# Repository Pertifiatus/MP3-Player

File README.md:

# MP3-Player

A compact **DIY music player**, smaller than an iPod Touch, built around a Raspberry Pi Compute Module 4 on a custom PCB. It syncs your **YouTube Music** library straight to the device, no home server needed.

## Concept

- **Front:** round GC9A01 display for menus and navigation
- **Back:** monochrome SSD1306 OLED for music visualizations
- **Audio:** mainly Bluetooth A2DP, plus a 3.5 mm headphone jack (ES8388 codec)
- **Controls:** button box (SX1509 GPIO expander) + IMU (QMI8658A) for orientation and shake gestures
- **Power:** Li-ion battery, USB-C charging (RT9466) with an 80% charge limit, fuel gauge (MAX17048), soft power button
- **Lighting:** SK6812 status ring

## Hardware

| Part | Details |
|---|---|
| Compute | Raspberry Pi CM4 Lite Wireless (boots from microSD), on 2× Hirose mezzanine connectors |
| Power | TPS63020 buck-boost, RT9466 charger, MAX17048 fuel gauge |
| Audio | ES8388 codec over I2S |
| Displays | GC9A01 (SPI0), SSD1306 (SPI4) |
| PCBs | Main board + ButtonBox, designed in KiCad (`KiCad/Projekt 1`) |
| Case | Fusion 360 (`CAD/Player.f3z`) |

## Software (`Software/`)

Python on Raspberry Pi OS, running as systemd services:

| File | Purpose |
|---|---|
| `main.py` | Main UI loop (front display, buttons, IMU) |
| `player.py` | Playback |
| `sync_youtube.py` | YouTube Music library sync |
| `connectivity.py` | WiFi / Bluetooth connections |
| `ui_state.py`, `ui_render.py` | UI state machine and rendering |
| `ui_views.py`, `ui_common.py` | Screen content as plain data, shared drawing helpers |
| `themes/` | 8 switchable designs (Einstellungen → Anzeige → Design): Klassik, Cybercore, Y2K, Glas, Neumorph, Bento, Pixelhaus, Cyberpunk |
| `preview_themes.py` | Preview sheet per design (`previews/`), `--bench` render timings |
| `fonts/`, `assets/` | Bundled OFL fonts, Pixelhaus house image |
| `buttonbox.py`, `qmi8658.py`, `es8388.py`, `max17048.py`, `rt9466.py` | Hardware drivers |
| `charge_control.py`, `power_button.py` | Charging logic and soft shutdown |
| `led_control.py`, `led_service.py` | Status ring LEDs |
| `setup_pi.sh`, `*.service`, `sdcard-boot-*` | Pi setup and boot configuration |
| `test_*.py` | Tests |

## Status

Work in progress. Board 2 boots reliably; the software bring-up and debugging of battery operation are ongoing. Detailed notes on hardware, pinout, `config.txt` and lessons learned are in [`CLAUDE.md`](CLAUDE.md) and [`Software/NOTES_FOR_PER.md`](Software/NOTES_FOR_PER.md).

## Repository structure

```
CAD/        Fusion 360 case
KiCad/      Main board + ButtonBox (schematics, PCB, 3D models)
Software/   Python application, drivers, services, tests
docs/       Design specs and plans (status ring, quick connect, design themes)
```

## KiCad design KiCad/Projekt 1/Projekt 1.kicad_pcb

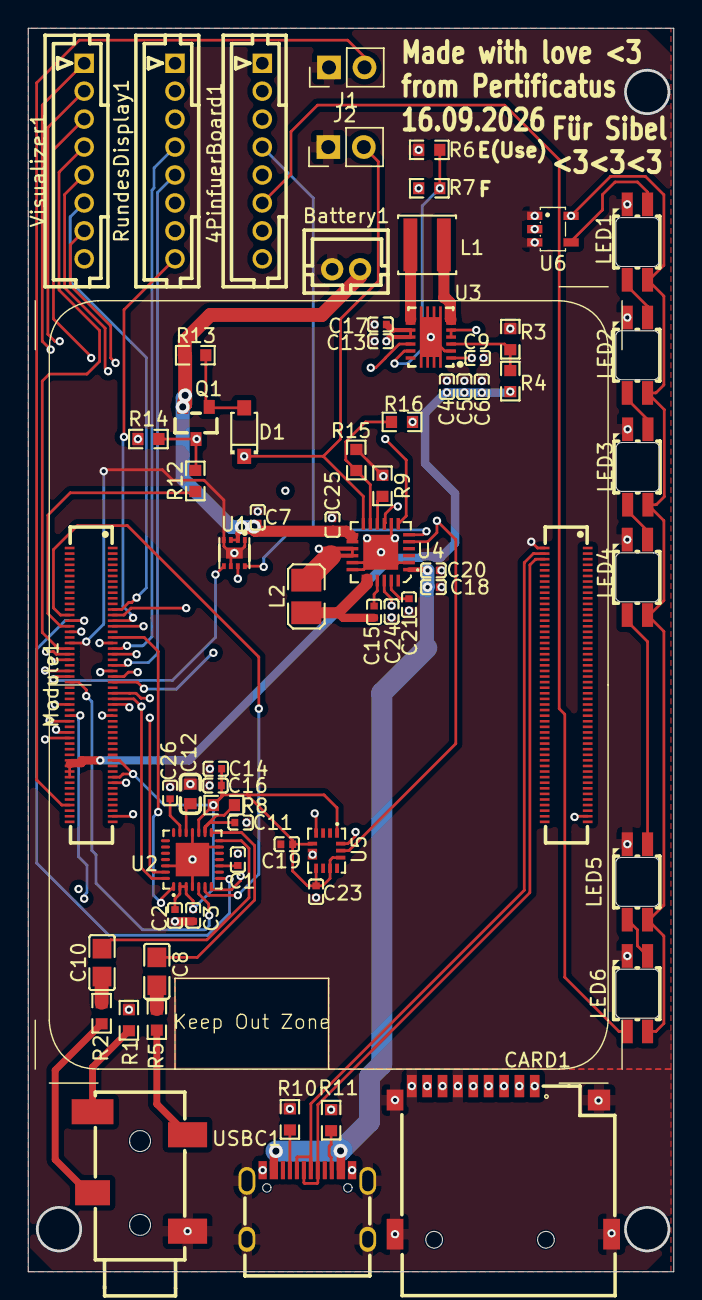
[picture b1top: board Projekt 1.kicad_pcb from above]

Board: 4 copper layers, 46.2 x 89.0 mm, 67 parts (0 on the bottom side), 74 nets.

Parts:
4PinfuerBoard1: CONN-TH_B8B-PH-K-S-LF-SN
AUDIO1: AUDIO-SMD_PJ-327C-4A
Battery1: CONN-TH_B2B-PH-K-S
C1, C18, C20: 2.2uF; C0402
C2, C3, C7, C9, C11, C14, C16, C19, C23: 100nF; C0402
C4, C5, C6: 22uF; C0402
C8, C10: 100uF; C0805
C12: 1uF; C0603
C13, C17, C25: 10uF; C0402
C15: 47nF; C0402
C21, C24, C26: 4.7uF; C0402
CARD1: TF-SMD_TF-PUSH
D1: SOD-123F_L2.7-W1.6-LS3.8-RD
J1: Boot Button; PinHeader_1x02_P2.54mm_Vertical
J2: Switch; PinHeader_1x02_P2.54mm_Vertical
L1: 1.5uH; IND-SMD_L4.0-W4.0-A
L2: 1uH; L2520
LED1, LED2, LED3, LED4, LED5, LED6: LED-SMD_4P-L3.2-W2.8-LS5.9_SK6812MINI-E
Module1: ComputeModule4-CM4; CONN-SMD_DF40HC-3.0-100DS-0.4V-51
Q1: SOT-23_L2.9-W1.3-P1.90-LS2.4-BR
R1, R10, R11: 5.1kΩ; R0603
R2, R5: 33Ω; R0603
R3: 180kΩ; R0603
R4: 1.6MΩ; R0603
R6, R7: 0Ω; R0603
R8: 10Ω; R0603
R9: 178Ω; R0603
R12: 220Ω; R0603
R13, R14: 100kΩ; R0603
R15, R16: 50kΩ; R0603
RundesDisplay1: CONN-TH_B8B-PH-K-S-LF-SN
U1: TDFN-8_L2.0-W2.0-P0.50-BL-EP1.2
U2: QFN-28_L4.0-W4.0-P0.45-BL-EP
U3: VSON-14_L4.0-W3.0-P0.50-BL-EP_TI_DSJ
U4: WQFN-24_L4.0-W4.0-P0.50-TL-EP2.5
U5: LGA-14_L3.0-W2.5-P0.50-TL
U6: SOT-23-5_L3.0-W1.7-P0.95-LS2.8-BR
USBC1: USB-C_SMD-TYPE-C-31-M-12_1
Visualizer1: CONN-TH_B8B-PH-K-S-LF-SN

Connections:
GND: AUDIO1.1, Battery1.2, C1.2, C2.1, C3.1, C4.2, C5.2, C6.2, C7.1, C9.1, C11.2, C12.2, C13.1, C14.2, C16.1, C17.1, C18.1, C19.1, C20.1, C21.2, C23.1, C24.1, C25.1, C26.1, CARD1.6 (VSS), CARD1.10, CARD1.11, CARD1.12, CARD1.13, CARD1.CD, J1.1, J2.1, LED1.1 (GND), LED2.1 (GND), LED3.1 (GND), LED4.1 (GND), LED5.1 (GND), LED6.1 (GND), Module1.35 (ID_SC), Module1.101 (USB_OTG_ID), Module1.198 (GND), R1.2, R3.2, R6.1, R9.1, R10.1, R11.1, R14.1, R15.2, U1.1 (CTG), U1.4 (GND), U1.6 (QSTRT), U1.9 (EP), U2.4 (DGND), U2.13 (HPGND), U2.18 (AGND), U2.26 (CE), U2.29 (EP), U3.2 (GND), U3.15 (PGND), U4.2 (PSEL), U4.8 (OTG), U4.17 (PGND), U4.18 (PGND), U4.25 (EP), U5.6 (GND), U5.7 (GND), U6.1 (OE#), U6.3 (GND), USBC1.1 (EH), USBC1.2 (EH), USBC1.3 (EH), USBC1.4 (EH), USBC1.A1B12 (GND), USBC1.B1A12 (GND)
unnamed: 4PinfuerBoard1.3, Module1.98 (GND), RundesDisplay1.3, Visualizer1.3
unnamed: AUDIO1.2, R5.1
unnamed: AUDIO1.3, R2.1
unnamed: AUDIO1.4, R1.1
unnamed: C8.1, R5.2
unnamed: C10.1, R2.2
unnamed: C15.2, L2.1, U4.19 (LX), U4.20 (LX)
unnamed: CARD1.2 (CD/DAT3), Module1.61 (SD_DAT3)
unnamed: CARD1.5 (CLX), Module1.57 (SD_CLK)
unnamed: CARD1.3 (CMD), Module1.62 (SD_CMD)
unnamed: CARD1.7 (DAT0), Module1.63 (SD_DAT0)
unnamed: CARD1.8 (DAT1), Module1.67 (SD_DAT1)
unnamed: CARD1.1 (DAT2), Module1.69 (SD_DAT2)
unnamed: 4PinfuerBoard1.1, CARD1.4 (VDD), Module1.86 (+3.3v_(Output)), RundesDisplay1.1, Visualizer1.1
unnamed: D1.2 (A), Q1.1 (G), R13.1
unnamed: D1.1 (K), J2.2, Module1.40 (GPIO9), U4.12 (#QON)
unnamed: J1.2, Module1.93 (nRPIBOOT)
unnamed: L1.1, U3.6 (L2), U3.7 (L2)
unnamed: L1.2, U3.8 (L1), U3.9 (L1)
unnamed: LED1.2 (DIN), U6.4 (Y)
unnamed: LED1.4 (DOUT), LED2.2 (DIN)
unnamed: 4PinfuerBoard1.5, C4.1, C5.1, C6.1, LED1.3 (VDD), LED2.3 (VDD), LED3.3 (VDD), LED4.3 (VDD), LED5.3 (VDD), LED6.3 (VDD), Module1.77 (+5v_(Input)), Module1.79 (+5v_(Input)), Module1.81 (+5v_(Input)), Module1.83 (+5v_(Input)), R4.2, U3.4 (VOUT), U3.5 (VOUT), U6.5 (VCC)
unnamed: LED2.4 (DOUT), LED3.2 (DIN)
unnamed: LED3.4 (DOUT), LED4.2 (DIN)
unnamed: LED4.4 (DOUT), LED5.2 (DIN)
unnamed: LED5.4 (DOUT), LED6.2 (DIN)
unnamed: 4PinfuerBoard1.6, LED6.4 (DOUT)
unnamed: 4PinfuerBoard1.4, Module1.58 (GPIO2), U1.8 (SDA), U2.27 (CDATA), U4.6 (SDA), U5.14 (SDA)
unnamed: 4PinfuerBoard1.2, Module1.56 (GPIO3), U1.7 (SCL), U2.28 (CCLK), U4.5 (SCL), U5.13 (SCL)
unnamed: Module1.54 (GPIO4), Visualizer1.7
unnamed: Module1.34 (GPIO5), U2.1 (MCLK)
unnamed: Module1.30 (GPIO6), Visualizer1.5
unnamed: Module1.37 (GPIO7), Visualizer1.4
unnamed: Module1.39 (GPIO8), RundesDisplay1.7
unnamed: Module1.44 (GPIO10), RundesDisplay1.5
unnamed: Module1.38 (GPIO11), RundesDisplay1.4
unnamed: Module1.31 (GPIO12), U6.2 (A)
unnamed: Module1.28 (GPIO13), RundesDisplay1.8
unnamed: Module1.29 (GPIO16), R12.1
unnamed: Module1.50 (GPIO17), U4.9 (CEB)
unnamed: Module1.49 (GPIO18), U2.5 (SCLK)
unnamed: Module1.26 (GPIO19), U2.7 (LRCK)
unnamed: Module1.27 (GPIO20), U2.8 (ASDOUT)
unnamed: Module1.25 (GPIO21), U2.6 (DSDIN)
unnamed: Module1.46 (GPIO22), U4.7 (INT)
unnamed: Module1.47 (GPIO23), U1.5 (ALRT#)
unnamed: Module1.45 (GPIO24), RundesDisplay1.6
unnamed: Module1.41 (GPIO25), RundesDisplay1.2
unnamed: Module1.24 (GPIO26), Visualizer1.6
unnamed: Module1.48 (GPIO27), Visualizer1.2
unnamed: C2.2, C3.2, C14.1, C16.2, C19.2, C23.2, Module1.78 (GPIO_VREF(1.8v/3.3v_Input)), Module1.84 (+3.3v_(Output)), R8.2, U2.2 (DVDD), U2.3 (PVDD), U2.17 (AVDD), U5.1 (SDO/SA0), U5.5 (VDDIO), U5.8 (VDD), U5.10 (CS-AUX), U5.12 (CS)
unnamed: Module1.36 (ID_SD), U5.4 (INT1)
unnamed: Module1.103 (USB2_N), USBC1.A7 (DN1), USBC1.B7 (DN2)
unnamed: Module1.105 (USB2_P), USBC1.A6 (DP1), USBC1.B6 (DP2)
unnamed: Q1.3 (D), R12.2, R14.2, U3.12 (EN)
unnamed: Battery1.1, C7.2, C25.2, Q1.2 (S), R13.2, U1.2 (CELL), U1.3 (VDD), U4.13 (BAT), U4.14 (BAT)
unnamed: C12.1, U2.19 (ADCVREF)
unnamed: C11.1, R8.1, U2.16 (HPVDD)
unnamed: C8.2, U2.15 (LOUT2)
unnamed: C10.2, U2.14 (ROUT2)
unnamed: C26.2, U2.20 (VMID)
unnamed: C1.1, U2.10 (VREF)
unnamed: R3.1, R4.1, U3.3 (FB)
unnamed: R6.2, R7.2, U3.13 (PS/SYNC)
unnamed: C9.2, C13.2, C17.2, L2.2, R7.1, U3.1 (VINA), U3.10 (VIN), U3.11 (VIN), U4.15 (SYS), U4.16 (SYS)
unnamed: C15.1, U4.21 (BTST)
unnamed: R9.2, U4.10 (ILIM)
unnamed: C24.2, R16.1, U4.22 (REGN)
unnamed: R15.1, R16.2, U4.11 (TS)
unnamed: C18.2, C20.2, U4.1 (VBUS), USBC1.A4B9 (VBUS), USBC1.B4A9 (VBUS)
unnamed: C21.1, U4.23 (VMID)
unnamed: R10.2, USBC1.A5 (CC1)
unnamed: R11.2, USBC1.B5 (CC2)

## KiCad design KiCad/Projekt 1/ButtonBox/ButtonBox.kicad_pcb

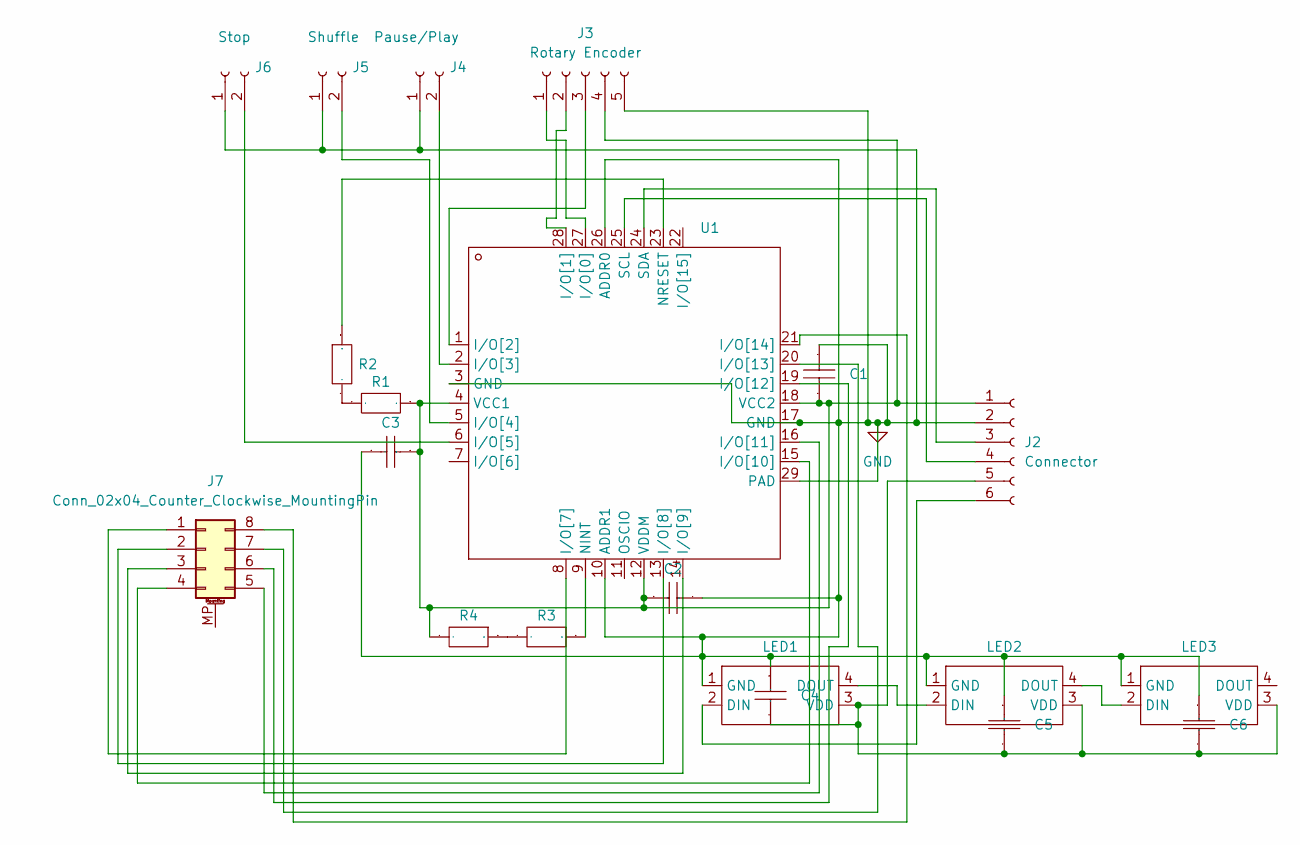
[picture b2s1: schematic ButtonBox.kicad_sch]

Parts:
C1, C2, C3, C4, C5, C6: 100nF; C0402; Manufacturer Part CC0402KRX5R9BB104; LCSC Part Name 100nF ±10% 50V
J2: Connector; 6Pin
J3: Rotary Encoder; 5PinRotary
J4: Pause/Play; 2PinKlick
J5: Shuffle; 2PinKlick
J6: Stop; 2PinKlick
J7: Conn_02x04_Counter_Clockwise_MountingPin; 8Pin
LED1, LED2, LED3: LED-SMD_4P-L3.2-W2.8-LS5.9_SK6812MINI-E; Manufacturer Part SK6812MINI-E; LCSC Part Name 工作电压5V、发光角度120°、灰度调节256级的RGB LED
R1, R2, R3, R4: 5.1kΩ; R0603; Manufacturer Part FRC0603F5101TS; LCSC Part Name 5.1kΩ ±1% 100mW 厚膜电阻
U1: QFN-28_L4.0-W4.0-P0.40-BL-EP; Manufacturer Part SX1509BIULTRT; LCSC Part Name SX1509BIULTRT

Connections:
GND: C1.2, C2.1, C3.2, C4.1, C5.1, C6.1, J2.2, J3.5, J4.1, J5.1, J6.1, LED1.1 (GND), LED2.1 (GND), LED3.1 (GND), U1.3 (GND), U1.10 (ADDR1), U1.17 (GND), U1.26 (ADDR0), U1.29 (PAD)
unnamed: C1.1, C2.2, C3.1, J2.1, J3.4, R1.1, R4.2, U1.4 (VCC1), U1.12 (VDDM), U1.18 (VCC2)
unnamed: J2.3, U1.24 (SDA)
unnamed: J2.4, U1.25 (SCL)
unnamed: C4.2, C5.2, C6.2, J2.5, LED1.3 (VDD), LED2.3 (VDD), LED3.3 (VDD)
unnamed: J2.6, LED1.2 (DIN)
unnamed: J3.1, U1.27 (I/O[0])
unnamed: J3.2, U1.28 (I/O[1])
unnamed: J3.3, U1.1 (I/O[2])
unnamed: J4.2, U1.2 (I/O[3])
unnamed: J5.2, U1.5 (I/O[4])
unnamed: J6.2, U1.6 (I/O[5])
unnamed: J7.1, U1.8 (I/O[7])
unnamed: J7.2, U1.13 (I/O[8])
unnamed: J7.3, U1.14 (I/O[9])
unnamed: J7.4, U1.15 (I/O[10])
unnamed: J7.5, U1.16 (I/O[11])
unnamed: J7.6, U1.19 (I/O[12])
unnamed: J7.7, U1.20 (I/O[13])
unnamed: J7.8, U1.21 (I/O[14])
unnamed: LED1.4 (DOUT), LED2.2 (DIN)
unnamed: LED2.4 (DOUT), LED3.2 (DIN)
unnamed: R1.2, R2.2
unnamed: R3.2, R4.1
unnamed: R3.1, U1.9 (NINT)
unnamed: R2.1, U1.23 (NRESET)

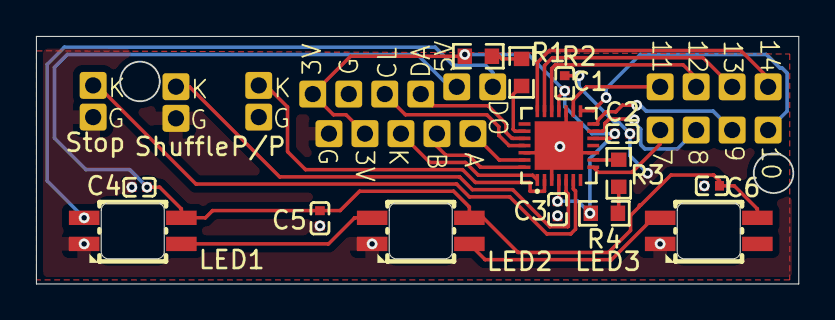
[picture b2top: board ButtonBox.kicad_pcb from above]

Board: 2 copper layers, 42.3 x 13.8 mm, 20 parts (0 on the bottom side), 26 nets.
